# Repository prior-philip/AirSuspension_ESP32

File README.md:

# AirSuspension Controller — ESP32-S3 SuperMini

Two-channel air suspension levelling controller for a campervan rear axle.
Reads two analog ride-height sensors, drives four valves (inflate/deflate per
side) from a tank with pressure-switched compressor, and shows state on a
128×128 SH1107 OLED and an on-demand WiFi web dashboard.

**Current release:** `Version v261028_1313`
`ESP32-S3 SuperMini | CAL | ManualMode | WiFi | OTA | flatBagInit | noPulsing`

---

## System overview

The controller replaces the vehicle's complete original air-suspension
control equipment. It consists of two boards connected by one shielded
cable, plus off-the-shelf parts:

```
  CABIN (left of steering wheel)                            REAR AXLE

  Fuse box 12 V ──► ┌───────────┐       shielded 12-core       ┌───────────┐
                    │    FCU    │ DE-9 #2 ───────────────────► │    RCU    │──► 4 valves (12 V)
  OLED SH1107 ──┐   │ ESP32-S3  │                  12-pin IP68 │  5 V sup. │──► 2 ride-height
  OEM buttons ──┴─► │ 4 MOSFETs │ DE-9 #1                      │  dividers │    sensors (5 V)
                    └───────────┘                              └───────────┘
                                                    Air springs (L/R) ◄── valves ◄── tank
  Compressor + tank with its own pressure switch:
  independent 12 V circuit, not controlled by this firmware.
```

### Components

| Component | Location | Part / specification | Connects to | Details |
|-----------|----------|----------------------|-------------|---------|
| **FCU** (Front Control Unit) | Cabin, next to the fuse box left of the steering wheel | Own PCB: ESP32-S3 SuperMini, 4 × IRLZ44N low-side valve MOSFETs, 12 V → 3.3 V step-down | 12 V from the fuse box; DE-9 #1 (display/buttons); DE-9 #2 (cable to RCU) | [`hardware/FCU`](hardware/FCU/README.md) |
| OLED display | Dashboard | I²C OLED 128 × 128, SH1107 controller, module MC01506 | FCU via DE-9 #1 | — |
| Buttons UP / DOWN | Dashboard | The vehicle's existing air-suspension buttons, reused | FCU via DE-9 #1 | — |
| Interconnect cable | Cabin → rear axle | Shielded, 12-core. DE-9 at the FCU, 12-pin IP68 connector (J4) at the RCU | FCU DE-9 #2 ↔ RCU J4 | Pinout: [RCU J4](hardware/RCU/README.md#connectors) |
| **RCU** (Rear Control Unit) | Rear axle | Own PCB: connector distribution, 12 V → 5 V sensor supply, 5 V → 3.3 V signal dividers | Cable (J4), valves (J3), sensors (J1) | [`hardware/RCU`](hardware/RCU/README.md) |
| Ride-height sensors (2) | Rear axle, left and right | Analog, 5 V supply. Original vehicle sensors, or BMW 37146870200 as replacement (see below) | RCU J1 | — |
| Valves (4) | Rear axle | 12 V solenoid valves, one inflate + one deflate per side; low-power coils, all four may be on together | RCU J3 (coil between +12 V and the switched line) | — |
| Compressor + tank | Vehicle | Any generic 12 V compressor with IPX water protection, ~6–8 bar, with its own pressure switch | Own fused 12 V circuit; air to the valves | — |
| Air springs (2) | Rear axle | Vehicle's air springs; inlet tubes restricted for slow, controllable flow | Valves | — |

### Ride-height sensors

- **Original sensors** connect directly to the RCU. They have not been tested
  with this controller yet but are expected to work.
- **Replacement:** **BMW 37146870200** is a good and cheaper fit (used on the
  2 Series F45, X5 F15/F85 and X6 F16/F86). Pinning and connector are the
  same as the original sensor.
- With the BMW sensor, the **sensor arm must be extended by 7 cm**. The longer
  arm reduces the angle the sensor turns over the full suspension travel, so
  it stays within its electrical range. Without it the sensor runs past its
  end stop with fully deflated or fully inflated air springs, and the reading
  wraps to the opposite end (see *Bag init* under Key behaviour).
- **Calibrate after fitting** any sensor or changing the arm (Menu →
  Calibrate). The right sensor is mounted mirrored, so its signal is
  inverted in firmware.

### Compressor

The compressor is not switched by the firmware: it fills the tank under the
control of its own pressure switch, and the controller only opens and closes
the valves between tank and air springs. Any generic 12 V compressor with
IPX water protection that reaches about 6–8 bar works. Fuse it separately.

## Pin assignment (firmware)

| Function      | GPIO | Notes                                        |
|---------------|------|----------------------------------------------|
| Sensor left   | 1    | ADC1                                         |
| Sensor right  | 2    | ADC1, sensor mounted inverted (always)       |
| Inflate left  | 4    |                                              |
| Deflate left  | 5    |                                              |
| Inflate right | 6    |                                              |
| Deflate right | 7    |                                              |
| I²C SDA / SCL | 8 / 9| SH1107 128×128 OLED                          |
| Button DOWN   | 12   | EXT1 deep-sleep wake, RTC pull-up held       |
| Button UP     | 13   | EXT1 deep-sleep wake, RTC pull-up held       |
| Status LED    | 48   | Shared red LED / WS2812 on the SuperMini     |

Low-power valves: all four valves may be energised together (no interlock).

## Repository layout

| Folder              | Content                                                  |
|---------------------|----------------------------------------------------------|
| `AirSuspension/`    | Arduino sketch (firmware)                                |
| `hardware/FCU/`     | KiCad project: Front Control Unit, see [its README](hardware/FCU/README.md) |
| `hardware/RCU/`     | KiCad project: Rear Control Unit, see [its README](hardware/RCU/README.md) |

Firmware releases are tagged `v*`; board revisions use `fcu-*` / `rcu-*`
tags (for example `fcu-rev2`) and do not trigger a firmware build. KiCad
backups, lock files and caches are git-ignored.

## Hardware designs

Two boards, both designed in KiCad 10, 2 copper layers, through-hole parts.

| Board | Role | Size | Revision |
|-------|------|------|----------|
| **FCU** (Front Control Unit) | ESP32-S3 SuperMini, four valve MOSFETs, 12 V to 3.3 V step-down, OLED / button / sensor connectors | 80.0 × 62.2 mm | 0.01 |
| **RCU** (Rear Control Unit) | Connector distribution at the rear axle: valves, ride-height sensors, 12 V to 5 V sensor supply, 5 V to 3.3 V signal dividers | 55.9 × 45.7 mm | not set in the title block |

```
 12 V ──► FCU ──► valves (low-side MOSFETs) ─┐
          ESP32-S3                            ├── cable ──► RCU ──► 4 valves
          OLED, 2 buttons       sensor signals ◄┘                         2 ride-height sensors
```

The schematics are the source of truth for pin assignments. The GPIO table
in the *Pin assignment (firmware)* section above is what the firmware uses; `hardware/FCU/README.md`
lists what the board wires up, and the two should match.

## Setup

1. Clone the repo and open `AirSuspension/AirSuspension.ino` in the Arduino IDE 2.x.
2. Install the ESP32 board package (core 3.3.x) and the **U8g2** library.
3. **Create your secrets file:** copy `AirSuspension/secrets.h.example` to
   `AirSuspension/secrets.h` and set your own `WIFI_AP_PASS` (at least 8
   characters). `secrets.h` is git-ignored and never committed. Without it
   the build stops with an error.
4. Select the board settings below, then compile and upload.

The example file contains a shared default password. Always set your own
before a board goes into a vehicle — either in `secrets.h`, or on the device
with the serial command `p` (see *Operation*). A password set with `p` is
stored in NVS on the board and takes precedence over `secrets.h`; it
survives deep sleep, power-off, USB re-flash and OTA updates. Only setting a
new one, or a full flash erase, replaces it.

### Automatic builds (GitHub Actions)

Every push to `S3` or `main`, and every pull request, is compiled by the
**Build** workflow (badge above). The `.bin` files are attached to each run
as artifacts. Pushing a tag such as `v1.0.0` also attaches them to a GitHub
Release.

CI builds use `secrets.h.example`, so the downloaded `.bin` files carry the
default password. For your own device, either compile locally with your own
`secrets.h`, or flash the CI build once and set your password with serial
`p` — it stays on the board across later OTA updates.

## Build settings (Arduino IDE 2.x, core 3.3.x)

Board `ESP32S3 Dev Module` · USB CDC On Boot `Enabled` · USB Mode
`Hardware CDC and JTAG` · Upload Mode `UART0 / Hardware CDC`. Do not debug
deep sleep with JTAG/gdb attached.

## Operation

| Input                      | Action                                        |
|----------------------------|-----------------------------------------------|
| Tap UP / DOWN              | Setpoint ±10 % (acts on release)              |
| Hold DOWN ≥ 1 s            | **OFF** standby (setpoint 45 = sentinel)      |
| Hold UP ≥ 1 s (while OFF)  | Resume last active setpoint                   |
| Both short                 | Menu: Manual · Calibrate · WiFi · Bag init    |
| Both ≥ 1 s                 | Reboot                                        |
| Serial `7 8 9 / 1 2 3`     | Valve pulses L↑ ↑↑ R↑ / L↓ ↓↓ R↓              |
| Serial `4 / 6`             | Setpoint −/+10 %                              |
| Serial `c`, `5`, `?`       | Calibration, reboot, help                     |
| Serial `w`                 | WiFi / web UI on / off                        |
| Serial `p`                 | Set WiFi password (`p` + Enter, then password + Enter; or `p <password>`) |

Web UI (auto-on for 20 min after power-on; menu → WiFi or serial `w`): dashboard with axle view, target slider (10 % steps),
dedicated OFF button, bag-init prompt/buttons, OTA update (Sketch → Export
Compiled Binary → Update tab).

## Key behaviour

- **Continuous regulation (ContReg).** A side out of band (±5 % parked,
  ±15 % driving, for 10 s) gets its valve held open until the fast estimate
  (median of last 3 oversampled reads) is within `STOP_MARGIN` of target;
  one `SETTLING_TIME` settle, then re-check.
- **Driving / rough terrain.** Deliberately *no* correction while the road
  keeps the signal bouncing through the band — level is restored after the
  van stops (60 s driving latch + 10 s entry delay).
- **Bag init (flatBagInit).** Detects the sensor-wrap signature
  (one side ≥ 95 %, other ≤ 5 % for 5 s), stops regulation and asks the user.
  Deflate probe 5 s → no change: inflate both sides 3 × 10 s (each side closes
  when OK) → change: extra 5 s deflates until both > 0 %. Failure/decline →
  FAULT (regulation blocked, survives sleep, auto-clears when readings are
  plausible, restart via menu/web).
- **Protections.** Regulation timeout 60 s → ERR (latched in RTC, cleared by
  setpoint change); anti-hunt lockout after 3 × no progress (5 %/10 s);
  both-button release lock after manual exit / menu / calibration / bag-init
  cancel.
- **Power.** WiFi auto-starts on power-on and switches off after 20 min
  (manual WiFi stays on until switched off).
  Deep sleep after 120 s idle & stationary; 8 s timer sniff,
  30 min housekeeping wake; never sleeps while WiFi is on, in manual,
  calibration or a bag-init prompt/phase.

## Main tunables (`Config.h`)

| Constant                     | Value  | Meaning                                   |
|------------------------------|--------|-------------------------------------------|
| `STATIONARY_WINDOW`          | 5 %    | Parked tolerance band                     |
| `DRIVING_TOLERANCE`          | 15 %   | Driving tolerance band                    |
| `DELAY_BEFORE_REGULATE`      | 10 s   | Continuous out-of-band time before acting |
| `STOP_MARGIN`                | 2 %    | Close valve this far before target — set ≈ measured coast |
| `SETTLING_TIME`              | 500 ms | Single settle after a correction          |
| `REGULATION_TIMEOUT`         | 60 s   | Max correction time → ERR                 |
| `DISPLAY_UPDATE_REGULATING`  | 250 ms | OLED refresh while a valve is open        |
| `AVERAGE_WINDOW`             | 15     | Slow average (display, driving, sleep)    |
| `BAGINIT_ENABLED`            | true   | Set false on the bench with floating inputs |

---

## Changelog

Newest first. Each release updates `VERSION` (`Version vYYMMDD_HHMM`) and the
one-line `DESCR` in the `.ino`.

### v261028_1313 — Change WiFi password over serial (`p`)
- New serial command `p`: type `p` + Enter, then the new password + Enter —
  or in one line `p <password>`. WPA2 rules: 8–63 printable characters;
  anything else is rejected and the old password stays. 60 s without input
  cancels. Non-blocking: regulation, display and watchdog keep running.
- Stored in NVS (`Preferences`, namespace `wifi`, key `appass`) and takes
  precedence over `WIFI_AP_PASS` from `secrets.h`; survives deep sleep,
  power-off, USB re-flash and OTA. No reset keyword — set a new password, or
  a full flash erase returns to the `secrets.h` default.
- If WiFi is on, the access point restarts immediately with the new password
  (connected devices must reconnect); a running 20 min power-on auto-off
  timer is kept. If WiFi is off, it applies at the next start.
- The new password is echoed once in serial for confirmation.

### v261028_1301 — Serial `w` restored (fix)
- **Fix:** the serial `w` / `W` command (WiFi on/off, added in v261024_1151)
  was missing on the `S3` branch — an older `SerialControl.h` had been
  committed. Restored, including the `w=WiFi on/off` help text. Same path as
  Menu → WiFi (`toggleWiFi()`).

### v261026_1151 — Display retry only when missing, faster boot, WiFi password in `secrets.h`
- **Display:** the forced full re-init every 60 s while the display was
  healthy is removed. The display is now re-initialised only when the 5 s
  I²C probe fails, and retried every 60 s while it is missing
  (`DISPLAY_FORCED_REINIT` → `DISPLAY_RETRY_INTERVAL`). Saves a blocking
  re-init and a possible flicker every minute.
- **Boot:** waiting for a USB serial host shortened from 3 s to 0.5 s — there
  is no host in the car, so every boot was 2.5 s slower than needed.
- **WiFi password** moved out of `Config.h` into the git-ignored `secrets.h`
  (template `secrets.h.example`); the build stops with an error if it is
  missing. See *Setup*.

### v261025_0828 — Auto-started WiFi switches off after 20 min
- WiFi auto-started at power-on now switches itself off after
  `WIFI_AUTOSTART_TIMEOUT_MS` (20 min, `Config.h`; 0 = never), then the
  normal 120 s idle rule applies before deep sleep.
- Switching WiFi manually (Menu → WiFi, serial `w`) cancels the timeout —
  manually enabled WiFi stays on until switched off.
- An OTA upload cannot be interrupted by the timeout (the upload runs inside
  the web handler, the timeout check is outside it).

### v261024_1153 — WiFi auto-start on power-on
- WiFi / web UI start automatically after a **power-on** (battery connected,
  cold start) — not after deep-sleep wakes, reboots or crash resets.
- Stays on until switched off (Menu → WiFi or serial `w`); while on, the
  controller does not deep-sleep. Switch: `WIFI_AUTOSTART_ON_POWERON` in
  `Config.h`.
- Started at the end of `setup()` after display init; sensor buffers are
  re-primed afterwards so no RF-calibration sample enters the averages.

### v261024_1151 — WiFi toggle over serial
- New serial command `w` (or `W`): toggles WiFi / web UI on and off, same
  code path as Menu → WiFi (shared `toggleWiFi()` in the `.ino`). Prints
  `[Web] AP ON: AirSuspension IP: 192.168.4.1` / `[Web] AP OFF`.
- `?` help text lists `w=WiFi on/off`.

### v261022_2032 — Display/I²C can no longer cause a watchdog boot loop (fix)
- **Fix:** with the I²C bus stuck low (loose/shorted SDA/SCL, missing
  pull-up, hung OLED) `initDisplay()` blocked > 4 s — `u8g2.begin()` reports
  success unconditionally and runs ~100 transactions, each waiting for the
  50 ms default timeout — and the task watchdog reset the board endlessly
  (`E (4275) task_wdt`). Same at runtime via the display health watchdog.
- `recoverI2CBus()` now checks that SDA and SCL idle HIGH and reports a stuck
  bus; `initDisplay()` probes the display address with one transaction before
  `u8g2.begin()`. No ACK or stuck bus → controller runs **headless**
  (regulation, buttons, web UI unaffected) and retries every 60 s.
- I²C transaction timeout bounded to `I2C_TIMEOUT_MS` = 20 ms; watchdog fed
  between init attempts.
- Boot log no longer claims "Display: OK" when the OLED is absent.
- `SH1107_I2C_ADDR` moved from the `.ino` to `Config.h`.

### v260930_1343 — OTA hardening
- **Fix:** an aborted upload (browser closed, WiFi lost) left the watchdog
  disabled until the next reboot. Every OTA exit path now re-enables it.
- Upload start ends any regulation run and cancels a running bag init, so no
  stale activity resumes after a failed upload.
- Wrong-chip images rejected on the first chunk with a readable message
  (chip ID from the image header vs. this board).
- Update tab shows running version/partition and image vs. OTA-slot size;
  oversized images are refused in the browser before uploading.
- Real error text (e.g. "Not Enough Space") returned instead of "Update failed".
- New endpoint `GET /api/fwinfo`.

### v260930_1004 — Resume setpoint persists (fix)
- `lastActiveSetpoint` (target for hold-UP resume from OFF) is now stored in
  EEPROM (`EEPROM_LAST_ACTIVE_ADDR` = 19) and loaded on every boot/wake.
  Previously RAM-only → after deep sleep or power-off, resume went to 50 %.
- Web OFF button now stores the current setpoint for resume as well.
- Written only when entering OFF and only if changed; invalid content
  (fresh 0xFF, > 100, OFF sentinel) falls back to 50 %. Calibration block and
  checksum unaffected.

### v260930_0936 — Continuous regulation (Phase 2) + reliability fixes
**Regulation**
- Pulse train removed: valve held open per side until fast estimate is within
  `STOP_MARGIN` (2 %); single 500 ms settle, then re-check.
- New fast height estimate: median of last 3 reads (`leftFastPct/rightFastPct`).
- Every sensor read oversampled: 4 conversions, min/max dropped.
- A side only opens if the fast estimate confirms it is still off target
  (prevents re-open chatter while the slow average catches up).
- OLED refresh slowed to 250 ms while a valve is open (I²C blocking).
- OFF, bag init, lockout and manual-mode entry always abort a running
  correction (`abortRegulationRun()`).
- `REG_PULSE_TIME` removed; display shows "ADJ" instead of "PULSE".
- Simulated: 1 valve opening per correction (was 6–9), final error
  1.1–1.5 % (was 3.4–3.7 %), no overshoot/chatter with ±40-count noise.

**Fixes**
- Regulation timeout left `isRegulating` stuck → board never slept.
  Now stops cleanly; ERR latched in RTC (`rtc_regError`) so sleep/wake does
  not retry; cleared by setpoint change.
- Both-button release: exiting manual mode, cancelling the menu, leaving
  calibration or cancelling bag init with buttons still held reopened the
  menu or **rebooted**. Shared release lock (`armButtonReleaseLock()`).
  Blocking `delay(300)` on manual exit removed.

### Earlier changes (reconstructed, pre-changelog)
- **Bag init v2:** inflate both sides simultaneously 3 × 10 s with per-side
  cutoff (was alternating L,R,L,R,L,R).
- **Bag init v1:** out-of-range detection, prompt, deflate probe, inflate
  phase, retry prompt, FAULT with RTC persistence; menu entry + web card.
- Suppression (slope/rough/safe) code removed incl. the live slope rule in
  the sleep wake check; OFF mode no longer wakes to "regulate".
- Single-valve interlock added then removed (low-power valves fitted).
- OFF standby via long-press (hold DOWN = OFF, hold UP = resume); web OFF
  button; slider snaps to 10 %.
- Phase 1 settling: 1.5 s regulation pulse / 0.3 s settle for restricted tubes.
- WiFi enabled keeps the board awake (idle sleep was switching WiFi off).
- Sensor filter: outlier re-prime requires agreeing samples (fixes phantom
  1 % dips).
- Serial input: CR/LF skipped, no blind flush (keys no longer dropped).
- Menu loop feeds the watchdog.
- Deep sleep: calibration loaded before the wake check; button pull-ups held
  via RTC domain; wake reason reported after USB-CDC re-enumeration.

---

## Open items

**Bugs / inconsistencies (from code review)**
- Uncalibrated: wake check (`quickSensorRead`) maps 0–4095, normal operation
  200–3800 → false movement wakes.
- Manual mode does not pause the out-of-band timers → regulation restarts
  immediately after leaving manual mode.
- `isVehicleDriving()` has side effects and is called from Regulation,
  Display and Debug → detection depends on display/debug cadence.
- Debug prints right raw ADC before inversion; "Tol 15%" hardcoded.
- Calibration accepts a floating pin (`CAL_MIN_SAFETY_LOW = 0`); span check
  200 (load) vs 1000 (validate).
- LED writes in `Valves.h`/`SerialControl.h` are overridden by the loop.
- `REGULATION_TIMEOUT` also used as the driving latch.
- Anti-hunt threshold (5 %/10 s) not yet re-sized for restricted tubes.
- `bagInitRestore()` always restores reason "Out of range".
- Dead code: button ISRs + `wakeupFlag`, `powerSave.sleepCycles`, unused
  manual-mode fields/`downWasPressed`, commented blocks, stale comments
  (pin table, LED section, OFF stepping, `Sensors.h` header/thresholds).

**Hardware (details in the board READMEs)**
- Button GPIOs: the FCU PCB routes `Button_Up` to GPIO 12 and `Button_Down`
  to GPIO 13; the firmware defines `BUTTON_DOWN = 12`, `BUTTON_UP = 13`.
  Check the harness, or swap in one place ([FCU open items](hardware/FCU/README.md#open-items-to-check)).
- DE-9 #1 (display/buttons) and DE-9 #2 (FCU side of the RCU cable) pin
  assignments are not documented in the repository yet.
- FCU: BOM (`FCU.csv`) and Gerber/drill files are older than the board —
  regenerate before ordering. RCU: schematic has no title block/revision.

**Planned**
- OTA follow-ups (not built): rollback safety, LAN join + mDNS + ArduinoOTA,
  NVS settings tab, persistent log. Check partition scheme vs. sketch size.
- Measure flow rate and coast → tune `STOP_MARGIN`; measure loop time.
- Fit the 7 cm sensor arm extension (BMW 37146870200) so the electrical
  range covers the full air-spring travel; recalibrate afterwards.
- Broken bag / tube detection + pump-overheat protection (duty budget,
  per-side faults, "Clear fault" in menu/web, healthy side keeps working).

## Design decisions

- Right height sensor is always inverted (hardware); inversion not calibrated.
- No correction on rough terrain; level restored after stopping.
- OFF persists through reboot and deep sleep.
- Faults/errors are cleared by explicit user action, never silently by sleep.

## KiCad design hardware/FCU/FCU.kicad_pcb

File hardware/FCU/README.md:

# FCU — Front Control Unit

Controller board of the air suspension system. It carries the ESP32-S3
SuperMini, four low-side MOSFETs for the pneumatic valves, a plug-in
step-down module for the 3.3 V rail, and the connectors for the OLED, the
two buttons and the ride-height sensors.

| | |
|---|---|
| KiCad project | `FCU.kicad_pro` (KiCad 10) |
| Revision | 0.01 (schematic title block) |
| Board | 80.0 × 62.2 mm, 2 layers, 1.6 mm |
| Firmware | [`AirSuspension/`](../../AirSuspension) |

## Functions

- **MCU:** ESP32-S3 SuperMini module (U3).
- **Valve drivers:** four IRLZ44N logic-level MOSFETs (Q1–Q4), low-side
  switching. Each gate has a 100 Ω series resistor and a 10 k pulldown to
  GND, so valves stay off while the MCU boots or sleeps. Each valve coil has
  a 1N4003 flyback diode to +12 V (D1–D4).
- **Power:** 12 V input (P1/P2), 470 µF and 470 nF bulk/decoupling on 12 V.
  A plug-in step-down module (P2–P5, marked "3.3V out") makes the 3.3 V rail.
  D5 (1N4003) connects the SuperMini's 5 V pin to the 12 V rail, so USB power also feeds that rail. The
  schematic note says some step-down modules need an input voltage when the
  board is USB-powered, otherwise their output shorts 3.3 V to GND.
- **Sensor inputs:** two analog inputs with 47 pF filter capacitors. In the
  vehicle the sensors are powered from the RCU, which also divides their
  signals down to 3.3 V (see [`../RCU`](../RCU)). Connector J3 breaks out
  the two signals together with 3.3 V and GND.
- **Buttons:** UP and DOWN with 10 k pullups to 3.3 V. The schematic notes
  that the signals are lifted during deep sleep to prevent unintended wake-ups.

## Connectors

| Ref | Name | Pins |
|-----|------|------|
| P1 | Power In | 2×3 header: 12 V and GND pairs |
| J1 | Valve Power 12V | 2 pins, +12 V |
| J2 | Valve Ctrl | 8 pins: 1 L_UP, 3 L_DN, 5 R_UP, 7 R_DN, 8 GND (2, 4, 6 unconnected) |
| J3 | Sensor | 1 +3.3 V, 2 GND, 3 Sensor_L, 4 Sensor_R |
| J4 | OLED Display | 1 GND, 2 +3.3 V, 3 SCL, 4 SDA |
| P6 | Buttons | 1 Button_Down, 2 GND, 3 Button_Up |

## ESP32-S3 pin assignment (from the PCB netlist)

| Signal | GPIO | Function |
|--------|------|----------|
| Sensor_L | 1 | Left ride-height sensor (ADC1) |
| Sensor_R | 2 | Right ride-height sensor (ADC1) |
| Left_Inflate | 4 | Gate Q1 (net L_UP) |
| Left_Deflate | 5 | Gate Q2 (net L_DN) |
| Right_Inflate | 6 | Gate Q3 (net R_UP) |
| Right_Deflate | 7 | Gate Q4 (net R_DN) |
| SDA / SCL | 8 / 9 | OLED I²C |
| Button_Up | 12 | see check below |
| Button_Down | 13 | see check below |

Unused: GPIO 3, 10, 11, TX, RX.

## Open items to check

- **Button GPIOs.** The PCB wires `Button_Up` to GPIO 12 and `Button_Down`
  to GPIO 13. The firmware (`Config.h`) defines `BUTTON_DOWN = 12` and
  `BUTTON_UP = 13`. Either the buttons are wired crosswise on the harness, or
  UP and DOWN are swapped in one of the two places.
- **`FCU.csv` is out of date.** It lists an Arduino Nano, LM7805 and IRLU120,
  which are not in the current schematic. Regenerate the BOM from KiCad.
- **Fabrication files are older than the board.** The Gerber and drill files
  in `Documents/VW-1234-10001` date from October 2025, the board file from
  June 2026. Regenerate them before ordering.
- **Stray files.** `AirSuspension.kicad_pcb` has no matching project, and
  `FCU.xml` is an old netlist export.

## Files

| Path | Content |
|------|---------|
| `FCU.kicad_pro/.kicad_sch/.kicad_pcb` | KiCad project |
| `Documents/VW-1234-10001/` | Gerber, drill, placement files and a zip of the fabrication data |
| `Documents/VW-1234-20001/` | Schematic and assembly PDFs, netlist, layer PDFs |
| `Documents/FCU.pdf` | Current schematic PDF |
| `Documents/schemtic.pdf` | Older schematic PDF |

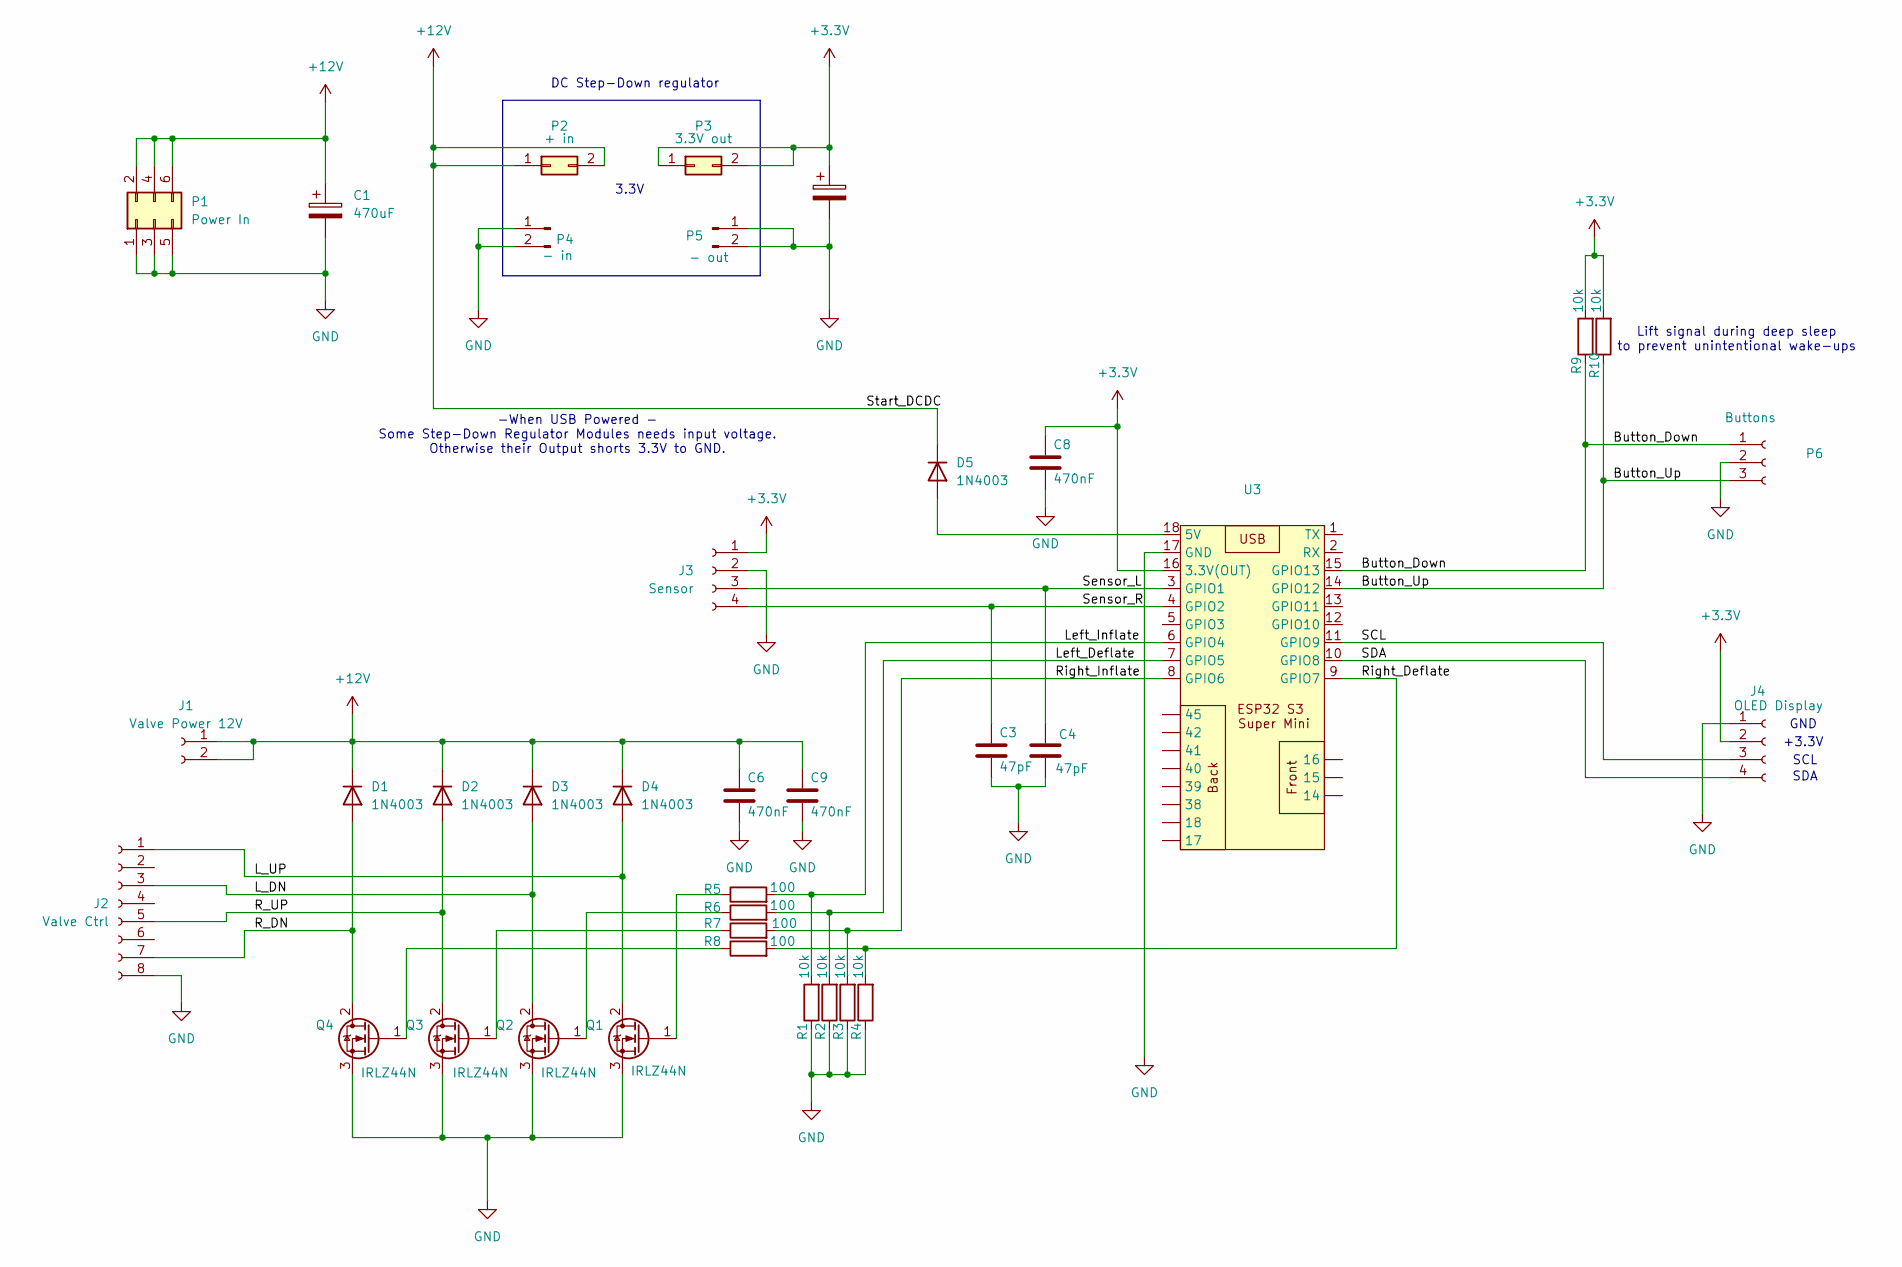
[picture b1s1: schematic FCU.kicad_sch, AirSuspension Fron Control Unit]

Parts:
C1: 470uF; CP_Radial_D6.3mm_P2.50mm
C2: 47uF; CP_Radial_D6.3mm_P2.50mm
C3, C4: 47pF; C_Rect_L7.0mm_W3.5mm_P5.00mm
C6, C8, C9: 470nF; C_Rect_L7.0mm_W3.5mm_P5.00mm
D1, D2, D3, D4: 1N4003; D_DO-41_SOD81_P2.54mm_Vertical_AnodeUp
D5: 1N4003; D_A-405_P10.16mm_Horizontal
J1: Valve Power 12V; PinSocket_1x02_P2.54mm_Vertical
J2: Valve Ctrl; PinSocket_1x08_P2.54mm_Vertical
J3: Sensor; PinSocket_1x04_P2.54mm_Vertical
J4: OLED Display; PinSocket_1x04_P2.54mm_Vertical
P1: Power In; PinHeader_2x03_P2.54mm_Vertical
P2: + in; PinHeader_2x01_P2.54mm_Horizontal
P3: 3.3V out; PinHeader_2x01_P2.54mm_Horizontal
P4: - in; PinHeader_1x02_P1.27mm_Vertical
P5: - out; PinHeader_1x02_P1.27mm_Vertical
P6: Buttons; PinHeader_1x03_P2.54mm_Vertical
Q1, Q2, Q3, Q4: IRLZ44N; TO-220-3_Vertical
R1, R2, R3, R4, R9: 10k; R_Axial_DIN0207_L6.3mm_D2.5mm_P10.16mm_Horizontal
R5, R6, R7, R8: 100; R_Axial_DIN0204_L3.6mm_D1.6mm_P5.08mm_Horizontal
R10: 10k; R_Axial_DIN0207_L6.3mm_D2.5mm_P2.54mm_Vertical
U3: ESP32-S3-SuperMini

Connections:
+3.3V: C2.1, C8.1, J3.1, J4.2, P3.1, P3.2, R9.2, R10.2, U3.16 (3.3V(OUT))
+12V: C1.1, C6.1, C9.1, D1.1 (K), D2.1 (K), D3.1 (K), D4.1 (K), D5.1 (K), J1.1, J1.2, P1.2, P1.4, P1.6, P2.1, P2.2
/Button_Down: P6.1, R9.1, U3.15 (GPIO13)
/Button_Up: P6.3, R10.1, U3.14 (GPIO12)
/L_DN: D3.2 (A), J2.3, Q2.2 (D)
/L_UP: D4.2 (A), J2.1, Q1.2 (D)
/Left_Deflate: R2.2, R6.2, U3.7 (GPIO5)
/Left_Inflate: R1.2, R5.2, U3.6 (GPIO4)
/R_DN: D1.2 (A), J2.7, Q4.2 (D)
/R_UP: D2.2 (A), J2.5, Q3.2 (D)
/Right_Deflate: R4.2, R8.2, U3.9 (GPIO7)
/Right_Inflate: R3.2, R7.2, U3.8 (GPIO6)
/SCL: J4.3, U3.11 (GPIO9)
/SDA: J4.4, U3.10 (GPIO8)
/Sensor_L: C4.1, J3.3, U3.3 (GPIO1)
/Sensor_R: C3.1, J3.4, U3.4 (GPIO2)
GND: C1.2, C2.2, C3.2, C4.2, C6.2, C8.2, C9.2, J2.8, J3.2, J4.1, P1.1, P1.3, P1.5, P4.1, P4.2, P5.1, P5.2, P6.2, Q1.3 (S), Q2.3 (S), Q3.3 (S), Q4.3 (S), R1.1, R2.1, R3.1, R4.1, U3.17 (GND)
unnamed: D5.2 (A), U3.18 (5V)
unnamed: Q1.1 (G), R5.1
unnamed: Q2.1 (G), R6.1
unnamed: Q3.1 (G), R7.1
unnamed: Q4.1 (G), R8.1

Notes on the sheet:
GND
-When USB Powered - Some Step-Down Regulator Modules needs input voltage. Otherwise their Output shorts 3.3V to GND.
DC Step-Down regulator
SDA
3.3V
+3.3V
Lift signal during deep sleep to prevent unintentional wake-ups
SCL

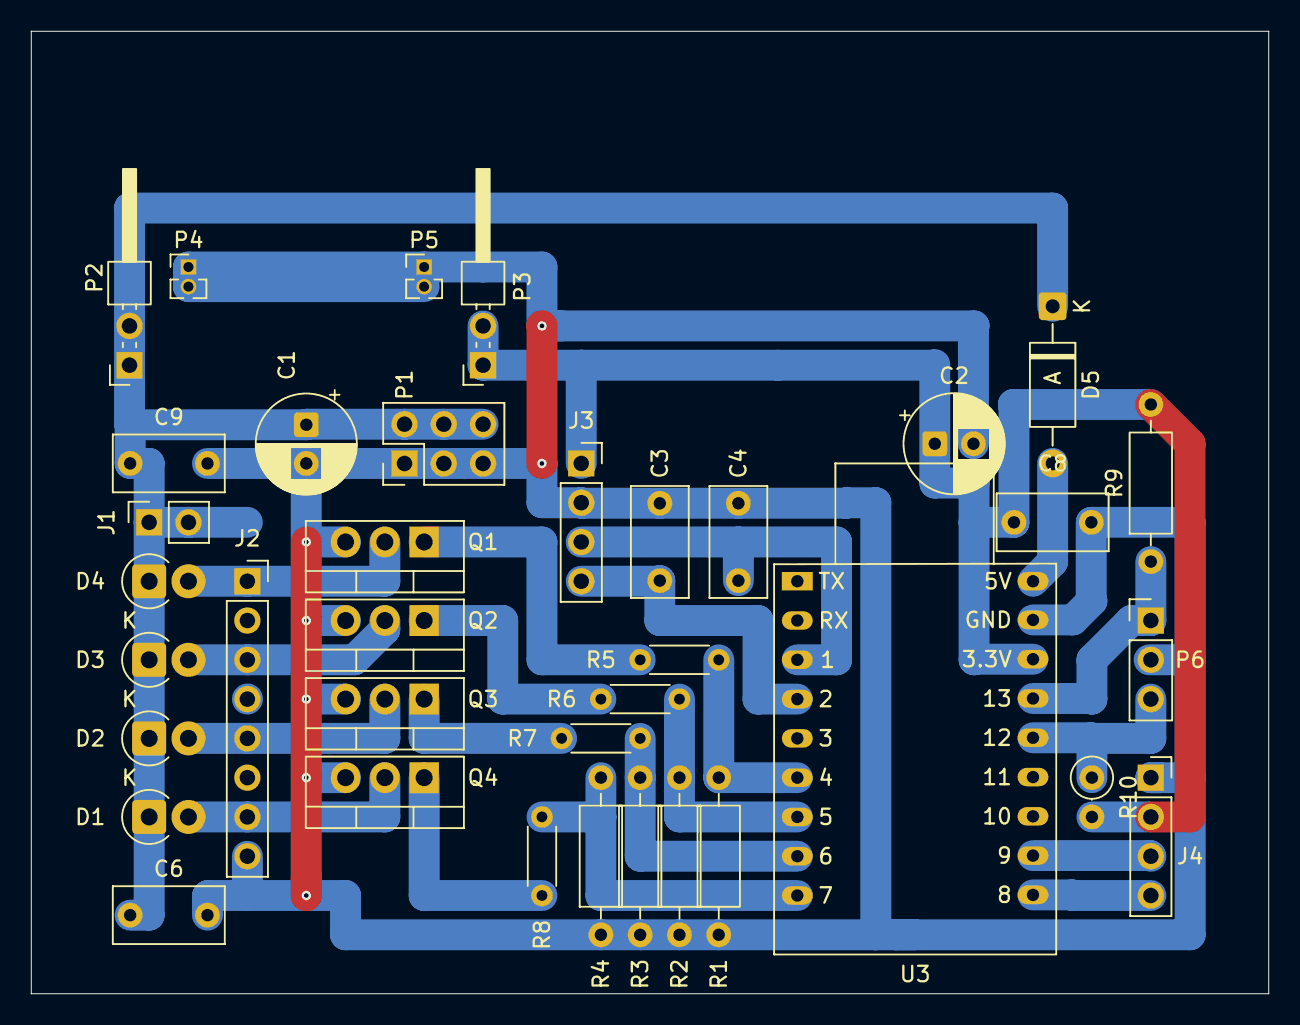
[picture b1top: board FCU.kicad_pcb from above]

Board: 2 copper layers, 80.0 x 62.2 mm, 37 parts (0 on the bottom side), 22 nets.

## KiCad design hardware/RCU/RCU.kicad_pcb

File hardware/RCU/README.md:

# RCU — Rear Control Unit

Small distribution board at the rear axle. It brings the valves and the two
ride-height sensors together on one 12-pin connector (J4) that leads to the FCU. It also makes
the 5 V sensor supply and divides the sensor signals down to a level the
ESP32-S3 can read.

| | |
|---|---|
| KiCad project | `RCU.kicad_pro` (KiCad 10) |
| Revision | not set (the schematic has no title block) |
| Board | 55.9 × 45.7 mm, 2 layers, 1.6 mm |
| Counterpart | [`hardware/FCU`](../FCU) |

## Functions

- **Connector distribution:** 12-pin input connector J4 (marked IP68) to the
  valve header J3 and the sensor header J1.
- **Sensor supply:** a plug-in step-down module (P2–P5, marked "5V out")
  makes +VSens (5 V) from the 12 V line. Capacitors C1–C6 decouple the
  12 V and 5 V rails.
- **Level shifter:** each sensor signal passes a 10 k series resistor and a
  20 k resistor to GND (R3/R1 for right, R4/R2 for left). A 5 V sensor
  output becomes about 3.3 V (5 V × 20 k / 30 k) at the FCU input.
- **Spare line:** J5 and J4 pin 11 carry an unused `SPARE` wire.

## Connectors

| Ref | Name | Pins |
|-----|------|------|
| J4 | Input connector IP68 (12 pin) | 1 +12 V, 2 L_INFLATE, 3 L_DEFLATE, 4 R_INFLATE, 5 R_DEFLATE, 6 +12 V, 7 Sensor_R, 8 GND, 9 Sensor_L, 10 GND, 11 SPARE, 12 not connected |
| J3 | Valves (8 pin) | 1 +12 V, 2 L_INFLATE, 3 +12 V, 4 L_DEFLATE, 5 +12 V, 6 R_INFLATE, 7 +12 V, 8 R_DEFLATE |
| J1 | Sensor (6 pin) | Two 3-pin sensors: 1 +VSens, 2 signal (to Sensor_R), 3 GND; 4 +VSens, 5 signal (to Sensor_L), 6 GND |
| J5 | Spare | SPARE |
| J2 | DE9 | in the schematic only: marked DNP, not placed on the board |

Valve coils sit between +12 V and the switched inflate/deflate lines, so the
FCU's low-side MOSFETs switch them.

## Signal names between the boards

| FCU net | RCU net | Meaning |
|---------|---------|---------|
| L_UP | L_INFLATE | Left valve, inflate |
| L_DN | L_DEFLATE | Left valve, deflate |
| R_UP | R_INFLATE | Right valve, inflate |
| R_DN | R_DEFLATE | Right valve, deflate |
| Sensor_L / Sensor_R | Sensor_L / Sensor_R | Sensor signals after the divider |

The cable between the boards is not part of this repository. Use the table
above when you build it.

## Open items to check

- **No revision.** The schematic has no title block, revision or date.
  Add them before the first release tag.

## Files

| Path | Content |
|------|---------|
| `RCU.kicad_pro/.kicad_sch/.kicad_pcb` | KiCad project |
| `Output/RCU.pdf` | Schematic PDF |

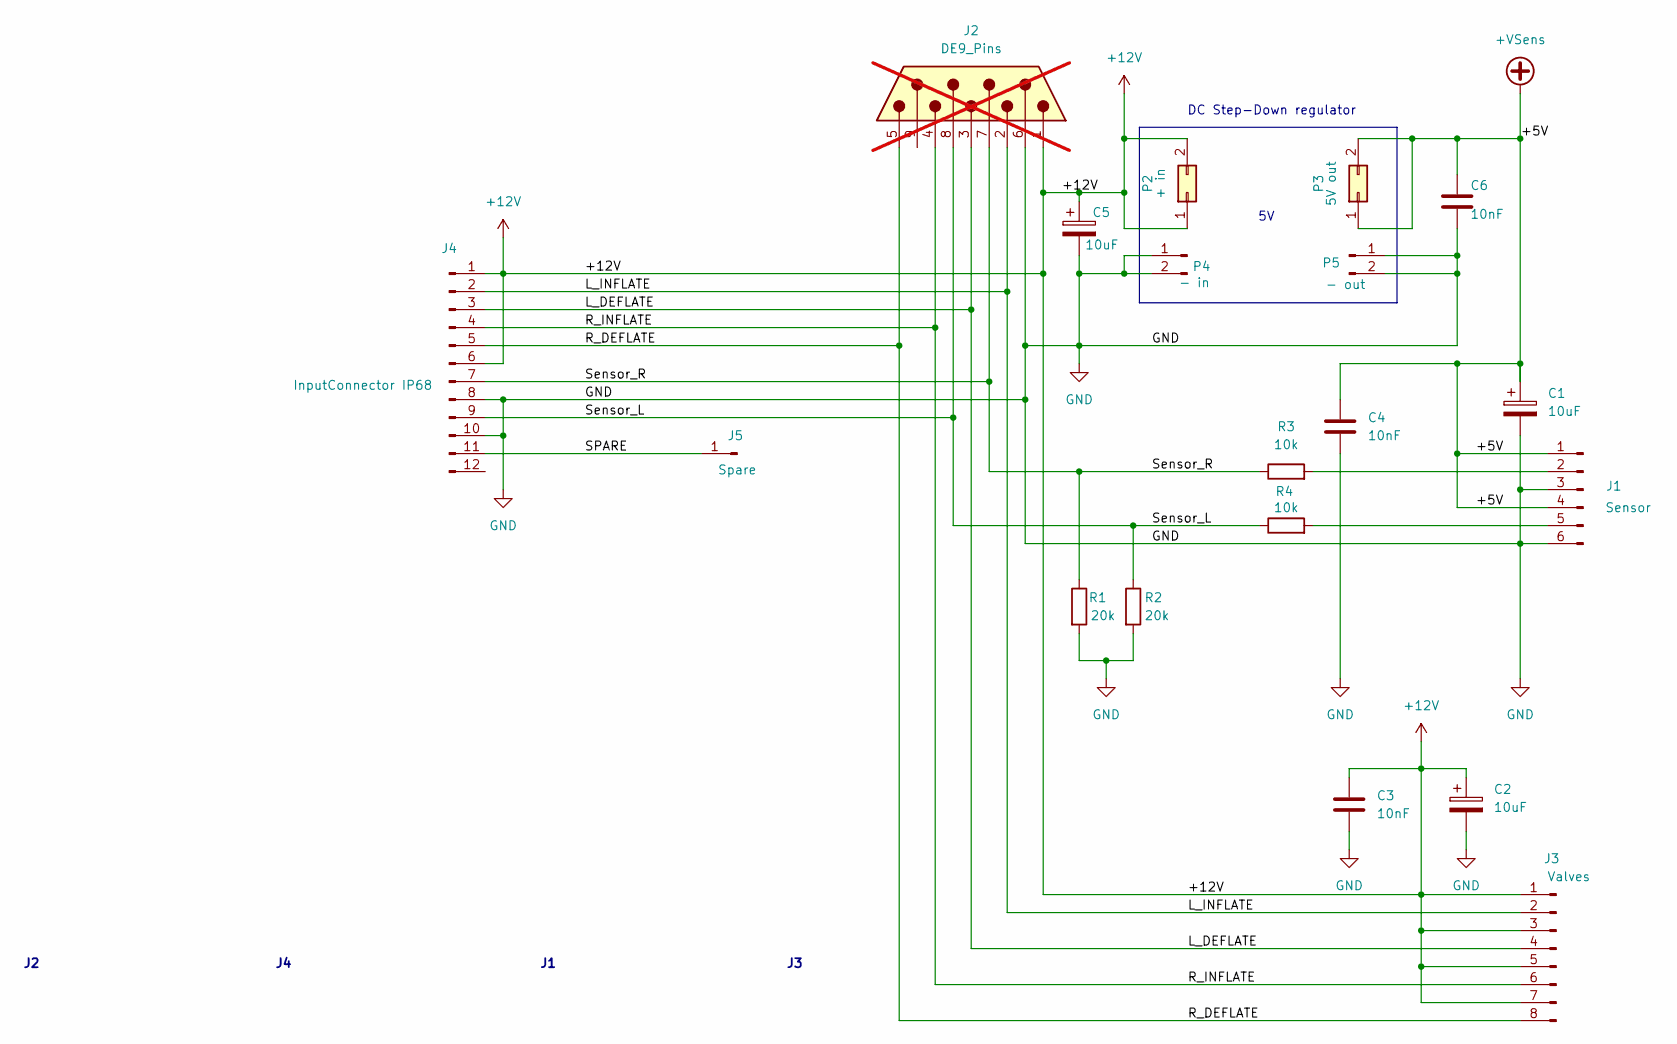
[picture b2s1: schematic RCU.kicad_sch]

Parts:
C1, C2, C5: 10uF; CP_Radial_D5.0mm_P2.50mm
C3, C6: 10nF; C_Disc_D4.3mm_W1.9mm_P5.00mm
C4: 10nF; C_Disc_D5.1mm_W3.2mm_P5.00mm
J1: Sensor; PinHeader_1x06_P2.54mm_Vertical
J2: DE9_Pins; DSUB-9_Pins_Vertical_P2.77x2.84mm; not fitted
J3: Valves; PinHeader_1x08_P2.54mm_Vertical
J4: InputConnector IP68; PinHeader_1x12_P2.54mm_Vertical
J5: Spare; PinHeader_1x01_P2.54mm_Vertical
P2: + in; PinHeader_2x01_P2.54mm_Horizontal
P3: 5V out; PinHeader_2x01_P2.54mm_Horizontal
P4: - in; PinHeader_1x02_P2.54mm_Vertical
P5: - out; PinHeader_1x02_P2.54mm_Vertical
R1, R2: 20k; R_Axial_DIN0207_L6.3mm_D2.5mm_P10.16mm_Horizontal
R3, R4: 10k; R_Axial_DIN0207_L6.3mm_D2.5mm_P10.16mm_Horizontal

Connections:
+12V: C2.1, C3.1, C5.1, J2.1, J3.1, J3.3, J3.5, J3.7, J4.1, J4.6, P2.1, P2.2
+VSens: C1.1, C4.1, C6.1, J1.1, J1.4, P3.1, P3.2
/L_DEFLATE: J2.3, J3.4, J4.3
/L_INFLATE: J2.2, J3.2, J4.2
/R_DEFLATE: J2.5, J3.8, J4.5
/R_INFLATE: J2.4, J3.6, J4.4
/SPARE: J4.11, J5.1 (Pin_1_1)
/Sensor_L: J2.8, J4.9, R2.1, R4.1
/Sensor_R: J2.7, J4.7, R1.1, R3.1
GND: C1.2, C2.2, C3.2, C4.2, C5.2, C6.2, J1.3, J1.6, J2.6, J4.8, J4.10, P4.1, P4.2, P5.1, P5.2, R1.2, R2.2
unnamed: J1.2, R3.2
unnamed: J1.5, R4.2

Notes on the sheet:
DC Step-Down regulator

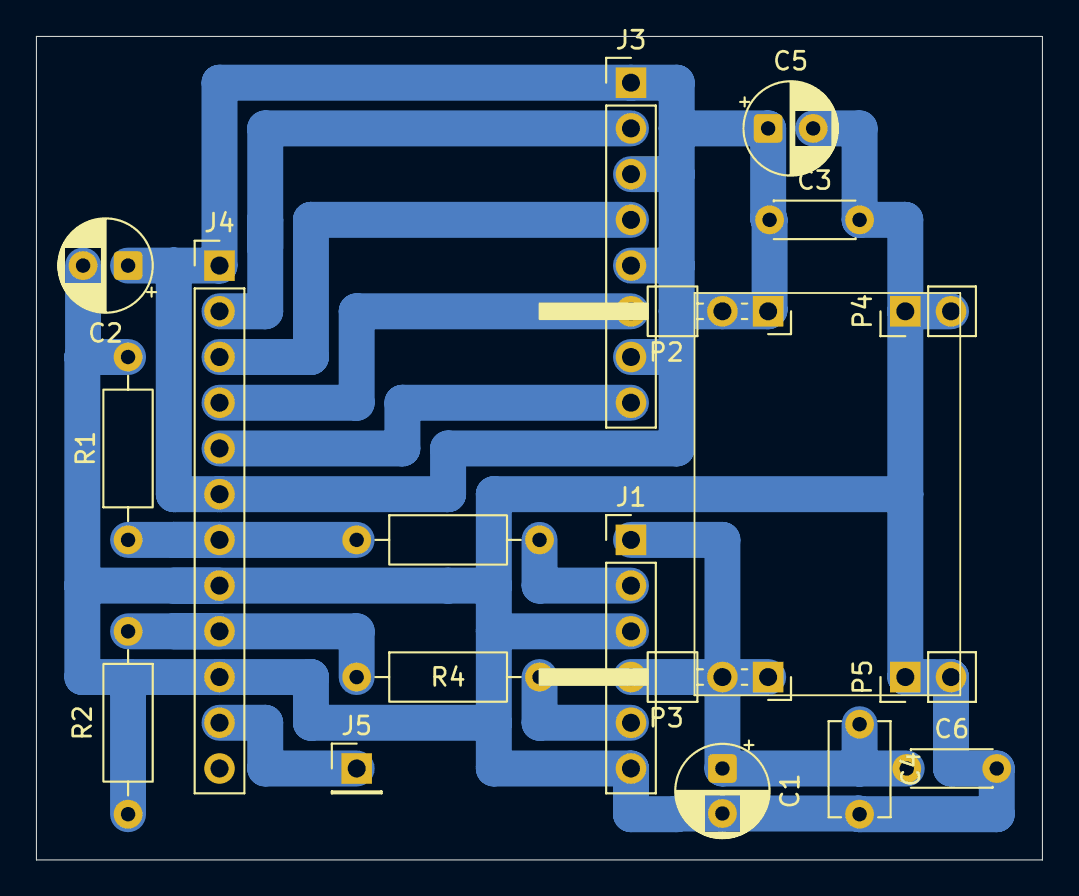
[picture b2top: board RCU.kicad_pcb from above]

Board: 2 copper layers, 55.9 x 45.7 mm, 18 parts (0 on the bottom side), 12 nets.

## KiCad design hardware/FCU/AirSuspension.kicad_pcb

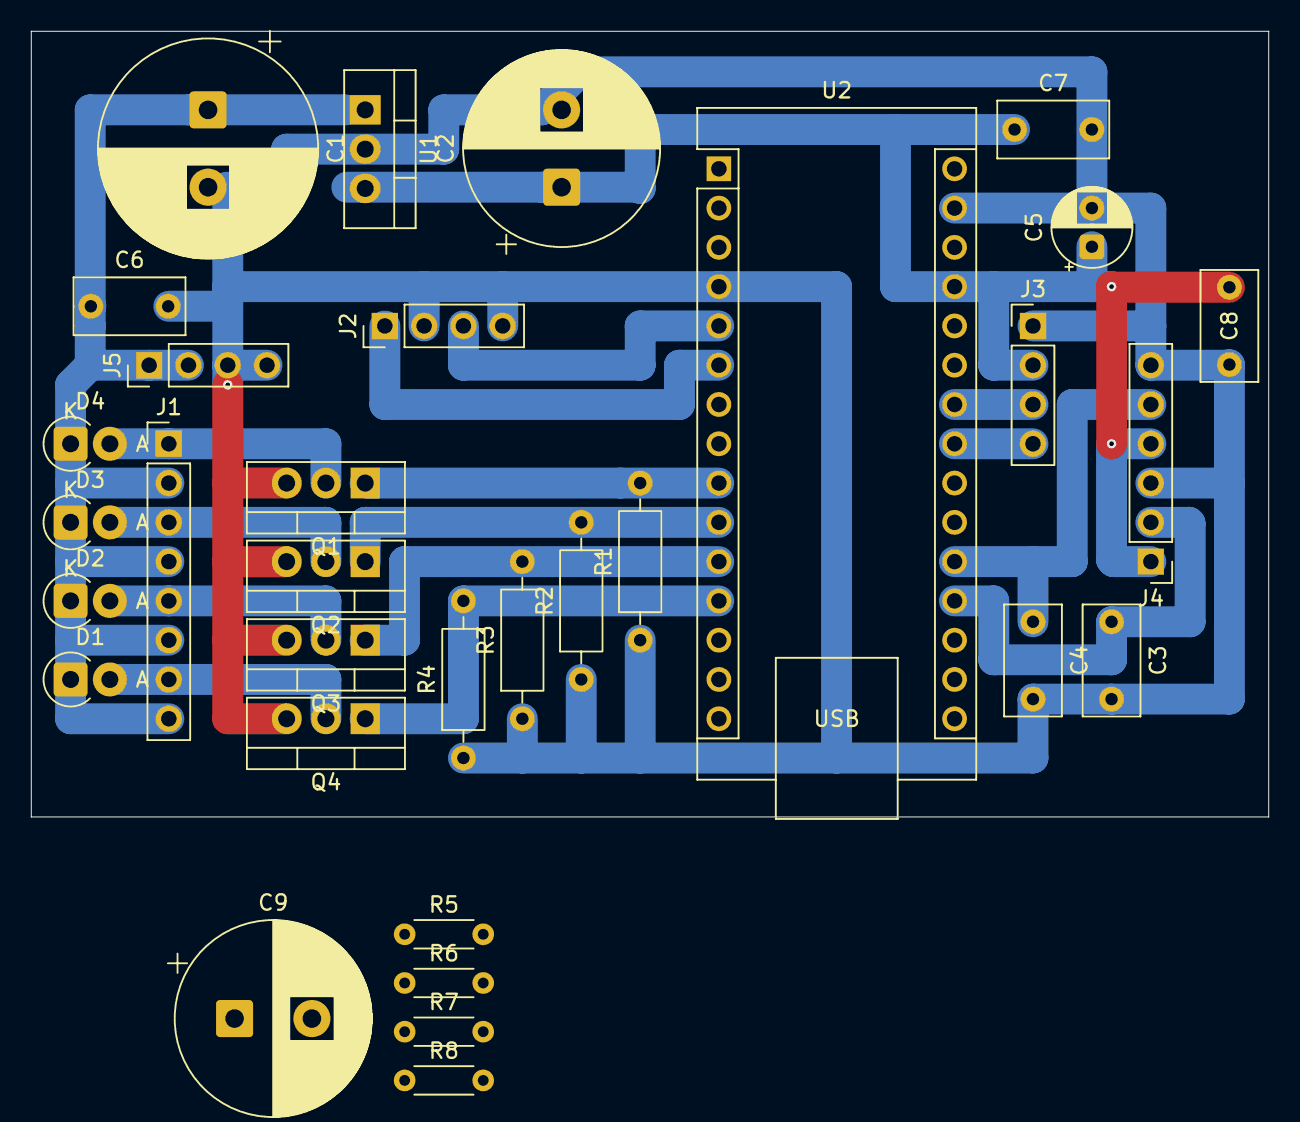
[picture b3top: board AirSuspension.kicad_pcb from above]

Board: 2 copper layers, 80.0 x 50.8 mm, 32 parts (0 on the bottom side), 21 nets.

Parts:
C1: 470uF; CP_Radial_D14.0mm_P5.00mm
C2: 47uF; CP_Radial_D12.5mm_P5.00mm
C3, C4: 47pF; C_Rect_L7.0mm_W3.5mm_P5.00mm
C5: 10uF; CP_Radial_D5.0mm_P2.50mm
C6: 47nF; C_Rect_L7.0mm_W3.5mm_P5.00mm
C7, C8: 470pF; C_Rect_L7.0mm_W3.5mm_P5.00mm
C9: 470uF; CP_Radial_D12.5mm_P5.00mm
D1, D2, D3, D4: 1N4003; D_DO-41_SOD81_P2.54mm_Vertical_AnodeUp
J1: Pneumatic Valves; PinHeader_1x08_P2.54mm_Vertical
J2: UP/DOWN Switch; PinHeader_1x04_P2.54mm_Vertical
J3: OLED Display; PinHeader_1x04_P2.54mm_Vertical
J4: NiveauSensor; PinHeader_1x06_P2.54mm_Vertical
J5: Power In; PinHeader_1x04_P2.54mm_Vertical
Q1, Q2, Q3, Q4: IRLU120; TO-220-3_Vertical
R1, R2, R3, R4: 10k; R_Axial_DIN0207_L6.3mm_D2.5mm_P10.16mm_Horizontal
R5, R6, R7, R8: 100; R_Axial_DIN0204_L3.6mm_D1.6mm_P5.08mm_Horizontal
U1: LM7805_TO220; TO-220-3_Vertical
U2: Arduino_Nano_v3.x; Arduino_Nano

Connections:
+5V: C2.1, C5.1, C7.1, C8.1, J3.2, J4.1, J4.4, U1.3 (VO), U2.27 (+5V)
+12V: C1.1, C6.1, C9.1, D1.1 (K), D2.1 (K), D3.1 (K), D4.1 (K), J1.2, J1.4, J1.6, J1.8, J5.1, J5.2, U1.1 (VI)
/Button_Down: J2.1, U2.6 (D3)
/Button_Up: J2.3, U2.5 (D2)
/Left_Deflate: D3.2 (A), J1.3, Q2.2 (D)
/Left_Inflate: D4.2 (A), J1.1, Q1.2 (D)
/Right_Deflate: D1.2 (A), J1.7, Q4.2 (D)
/Right_Inflate: D2.2 (A), J1.5, Q3.2 (D)
/SCL: J3.3, U2.24 (A5)
/SDA: J3.4, U2.23 (A4)
/Sens_L: C3.1, J4.2, U2.19 (A0)
/Sens_R: C4.1, J4.5, U2.20 (A1)
GND: C1.2, C2.2, C3.2, C4.2, C5.2, C6.2, C7.2, C8.2, C9.2, J2.2, J2.4, J3.1, J4.3, J4.6, J5.3, J5.4, Q1.3 (S), Q2.3 (S), Q3.3 (S), Q4.3 (S), R1.1, R2.1, R3.1, R4.1, U1.2 (GND), U2.4 (GND), U2.29 (GND)
unnamed: Q1.1 (G), R5.1
unnamed: Q2.1 (G), R6.1
unnamed: Q3.1 (G), R7.1
unnamed: Q4.1 (G), R8.1
unnamed: R1.2, R5.2, U2.9 (D6)
unnamed: R2.2, R6.2, U2.10 (D7)
unnamed: R3.2, R7.2, U2.11 (D8)
unnamed: R4.2, R8.2, U2.12 (D9)
